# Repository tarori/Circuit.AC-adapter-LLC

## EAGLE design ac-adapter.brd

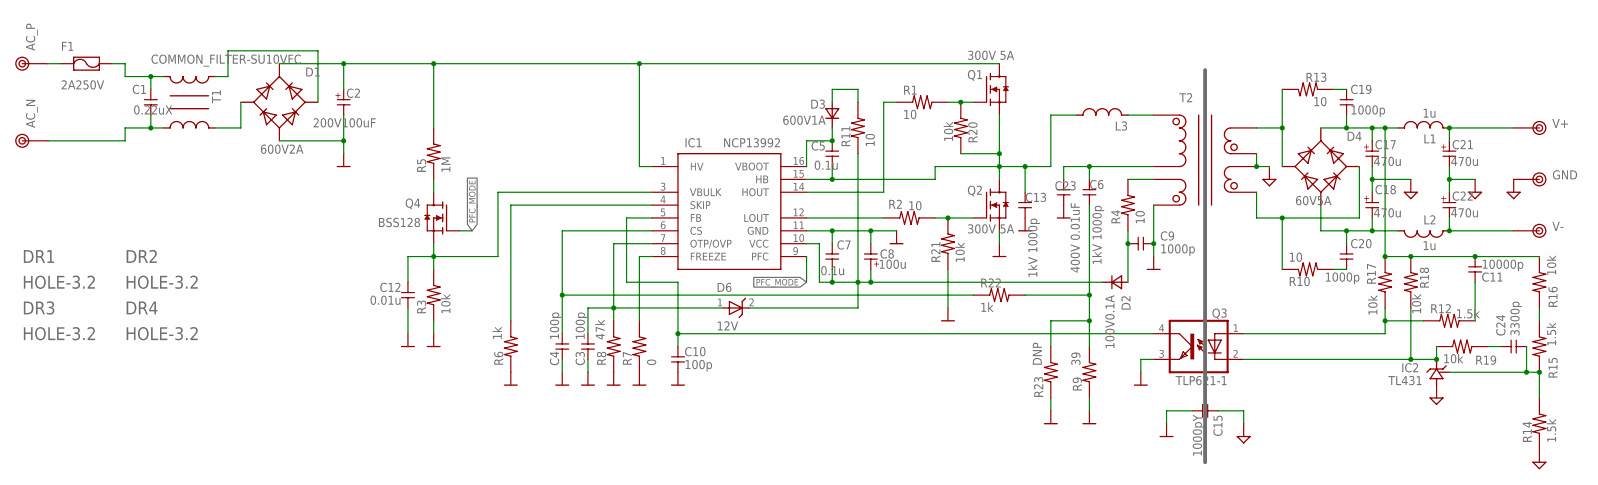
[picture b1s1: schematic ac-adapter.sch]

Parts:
C1: 0.22uX; X-CAPACITER
C2: 200V100uF; E5-16A2
C3, C4, C10: 100p; 1608
C5, C7: 0.1u; 1608
C6, C13: 1kV 1000p; C050
C8: 100u; E2.5-6.5
C9, C19, C20: 1000p; 1608
C11: 10000p; 1608
C12: 0.01u; 1608
C15: 1000pY; Y-CAPACITER
C17, C18, C21, C22: 470u; E5-10
C23: 400V 0.01uF; C125
C24: 3300p; 1608
D1: 600V2A; GBU8A
D2: 100V0.1A; SOD123
D3: 600V1A; D0204/7
D4: 60V5A; RBA-406
D6: 12V; SOD123
DR1, DR2, DR3, DR4: HOLE-3.2; HOLE_3.2
F1: 2A250V; FUSE-5
IC1: NCP13992; SO16-NCP13992
IC2: TL431; TO-92
L1, L2: 1u; L5-7,5
L3: L-PQ20; BPQ20/20
Q1, Q2: 300V 5A; TO-220
Q3: TLP621-1; DIL04
Q4: BSS128; SC59
R1, R2, R10, R13: 10; 2012
R3, R16, R17, R18, R19, R20, R21: 10k; 1608
R4, R11: 10; 1608
R5: 1M; 0204/7
R6, R22: 1k; 1608
R7: 0; 1608-J
R8: 47k; 1608
R9: 39; 1608
R12, R14, R15: 1.5k; 1608
R23: DNP; 1608
T1: COMMON_FILTER-SU10VFC; SU10VFC
T2: TRANSFORMAER_FLYBACK-PQ2620; BPQ26/20-1112CPFR
TP1: AC_P; TESTPIN-BIG
TP2: AC_N; TESTPIN-BIG
TP3: V+; TESTPIN-BIG
TP4: V-; TESTPIN-BIG
TP5: GND; TESTPIN-BIG

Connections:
GND: C15.1, C17.- (2), C18.+ (1), C21.- (2), C22.+ (1), IC2.2 (GND), R14.1, T2.9 (L3_P), T2.10 (L4_N), TP5.1
unnamed: C1.1, F1.2, T1.2
unnamed: Q1.1 (G), R1.2, R20.1
unnamed: C19.1, R13.1
unnamed: D1.3 (AC2), T1.1
unnamed: D1.2 (AC1), T1.4
unnamed: R15.2, R16.1
unnamed: C18.- (2), C20.1, D4.4 (V-), L2.2 (1)
unnamed: C6.1, C23.1, T2.3 (L1_N)
unnamed: Q2.1 (G), R2.1, R21.2
unnamed: C20.2, R10.2
unnamed: L3.6 (2), T2.1 (L1_P)
unnamed: IC1.8 (FREEZE), R7.2
unnamed: C3.1, D6.1 (A), IC1.7 (OTP/OVP), R8.2
unnamed: C4.1, IC1.6 (CS), R22.1
unnamed: IC1.4 (SKIP), R6.2
unnamed: IC1.14 (HOUT), R1.1
unnamed: IC1.12 (LOUT), R2.2
unnamed: C5.1, D3.2 (K), IC1.16 (VBOOT)
unnamed: C12.1, IC1.3 (VBULK), Q4.2 (S), R3.2
unnamed: C10.1, IC1.5 (FB), Q3.4 (COL)
unnamed: Q4.3 (D), R5.1
unnamed: R4.2, T2.6 (L2_N)
unnamed: C11.1, R12.2
unnamed: C9.1, D2.1 (A), R4.1
unnamed: D3.1 (A), R11.2
unnamed: C1.2, T1.3, TP2.1
unnamed: C6.2, R9.2, R22.2, R23.2
unnamed: IC2.3 (OUT), Q3.2 (C), R18.1, R19.1
unnamed: C24.2, IC2.1 (REF), R14.2, R15.1
unnamed: C24.1, R19.2
unnamed: Q3.1 (A), R12.1, R17.2
unnamed: D4.2 (AC1), R13.2, T2.7 (L3_N), T2.8 (L3_N)
unnamed: D4.3 (AC2), R10.1, T2.11 (L4_P), T2.12 (L4_P)
unnamed: F1.1, TP1.1
unnamed: C11.2, C17.+ (1), C19.2, D4.1 (V+), L1.2 (1), R16.2, R17.1, R18.2
PFC_MODE: IC1.9 (PFC), Q4.1 (G)
PGND: C2.- (2), C3.2, C4.2, C7.2, C8.- (2), C9.2, C10.2, C12.2, C13.2, C15.2, C23.2, D1.4 (V-), IC1.11 (GND), Q2.3 (S), Q3.3 (EMIT), R3.1, R6.1, R7.1, R8.1, R9.1, R21.1, R23.1, T2.5 (L2_P)
SW: C5.2, C13.1, IC1.15 (HB), L3.4 (1), Q1.3 (S), Q2.2 (D), R20.2
V+: C21.+ (1), L1.1 (2), TP3.1
V-: C22.- (2), L2.1 (2), TP4.1
VCC: C7.1, C8.+ (1), D2.2 (K), D6.2 (C), IC1.10 (VCC), R11.1
VH: C2.+ (1), D1.1 (V+), IC1.1 (HV), Q1.2 (D), R5.2

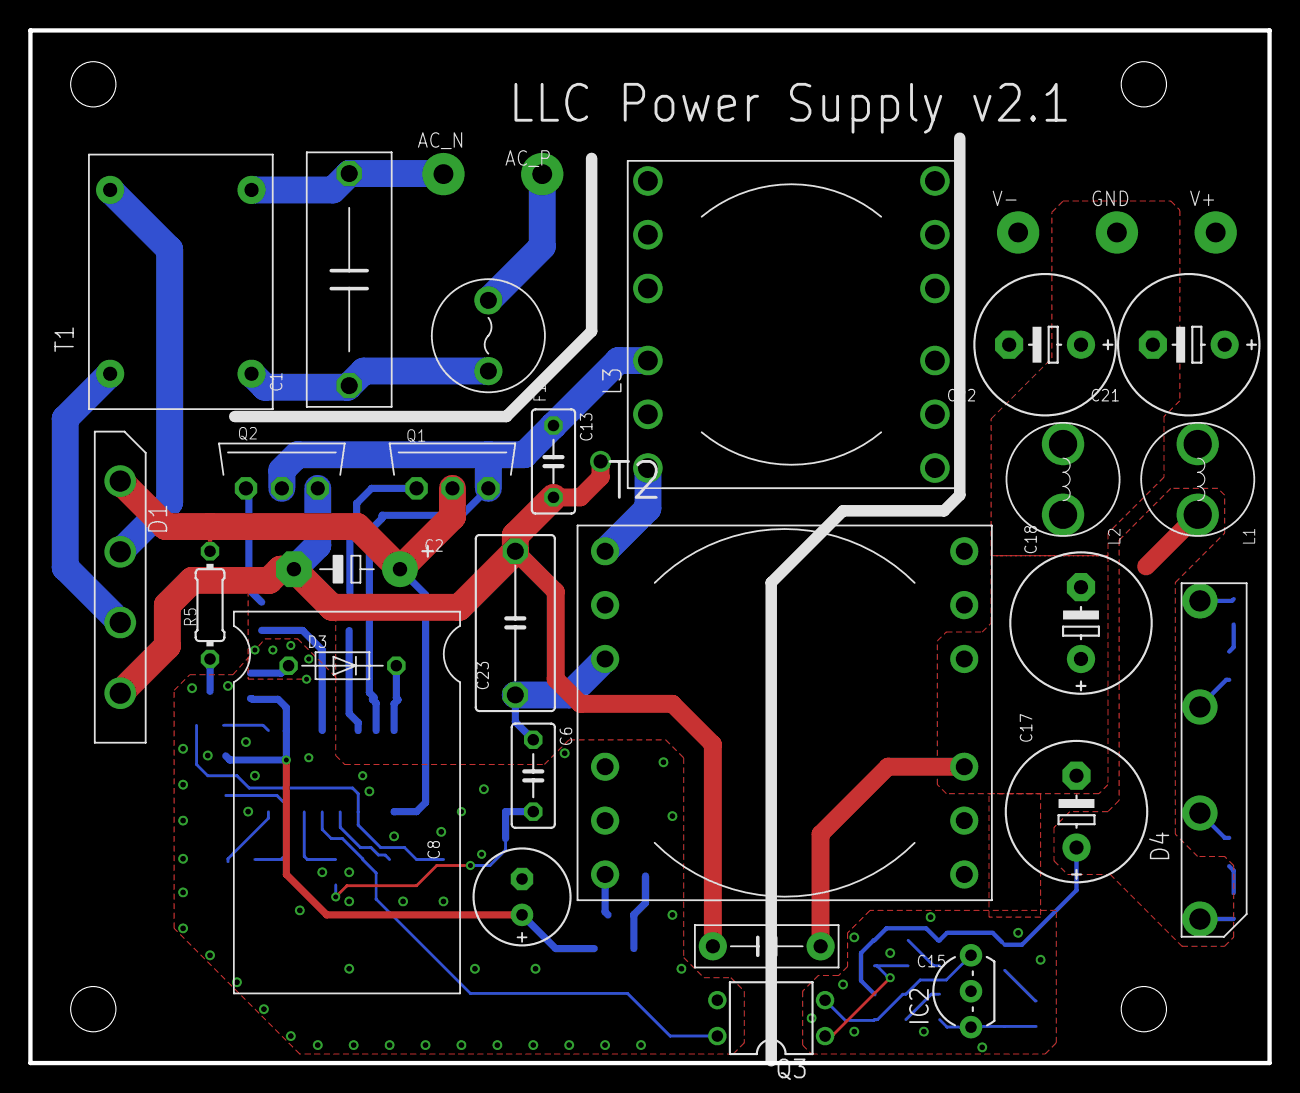
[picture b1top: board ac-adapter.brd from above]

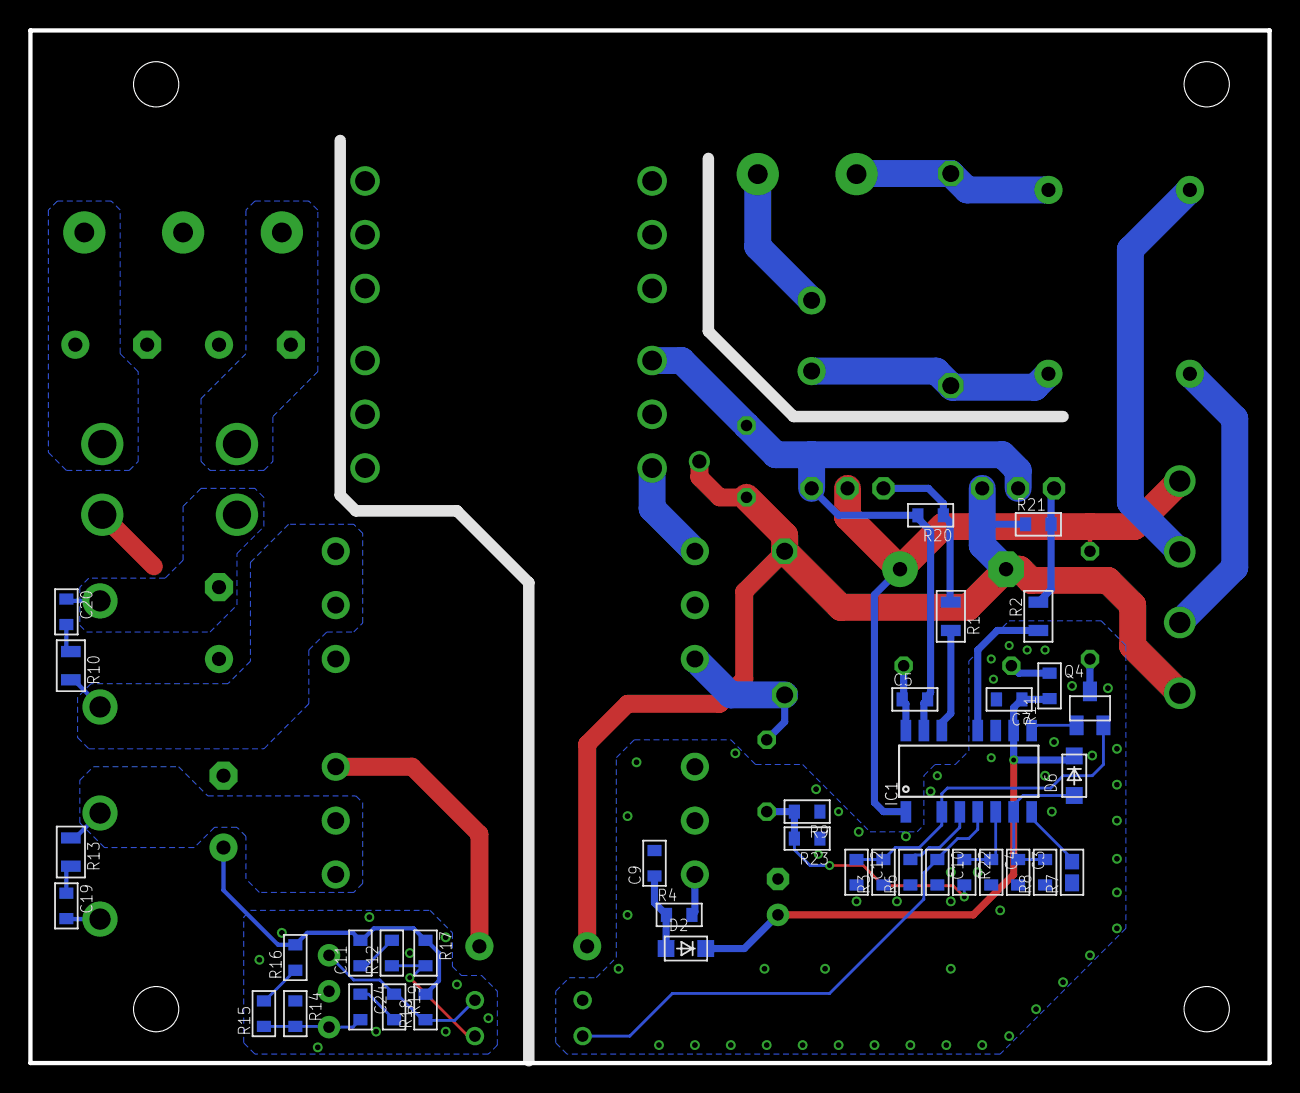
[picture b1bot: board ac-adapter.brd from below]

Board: 2 copper layers, 87.6 x 73.0 mm, 71 parts (37 on the bottom side), 43 nets.

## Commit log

2020-06-13 1次側の回路図
2020-06-13 こんな感じ
2020-06-14 電解コン大きく
2020-06-16 コモンモードフィルタ追加
2021-03-25 定数決まらん
2021-04-17 tiny fix
